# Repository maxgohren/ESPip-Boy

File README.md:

# ESPip-Boy
A smart watch based on the ESP32

# Features
* ESP32 MCU with full Bluetooth Classic
* SD Card storage
* TFT RGB Display
* Flashlight
* Microphone
* Sensors
  * Heart Rate & Blood Oxygen
  * Light Sensor (Auto Display Brightness)
  * Accelerometer (Auto Wakeup, Gestures) 
  * Magnetometer  (Compass)
* Controlled with Push-Button Rotary Encoder

# Planned Applications
* Compass
* Pedometer
* Map/Photo Display
* Clock
* Heart Rate Monitor
* Music Playback
* Bluetooth Manager
* System Monitor (CPU Tasks, SD Storage, RAM Usage etc.)

Powered by a LiPo, charged and programmed over USB

# V1.0 PCB Complete

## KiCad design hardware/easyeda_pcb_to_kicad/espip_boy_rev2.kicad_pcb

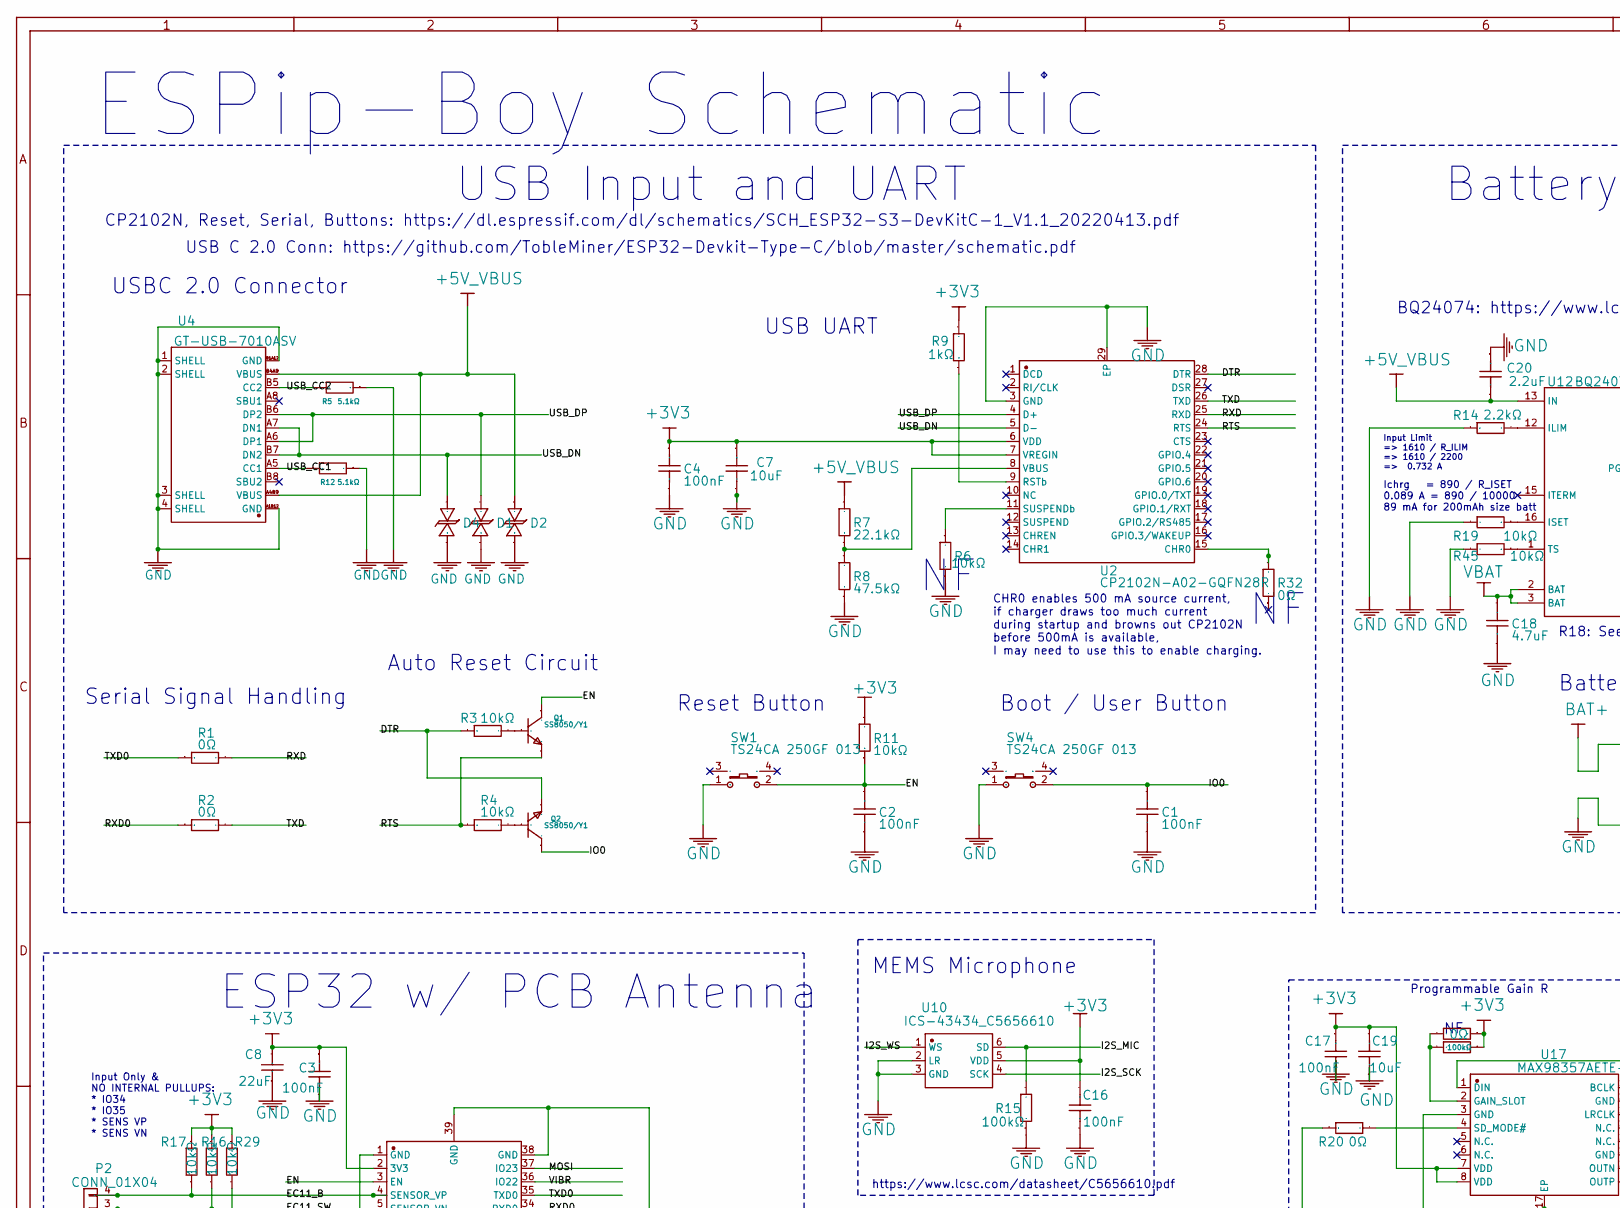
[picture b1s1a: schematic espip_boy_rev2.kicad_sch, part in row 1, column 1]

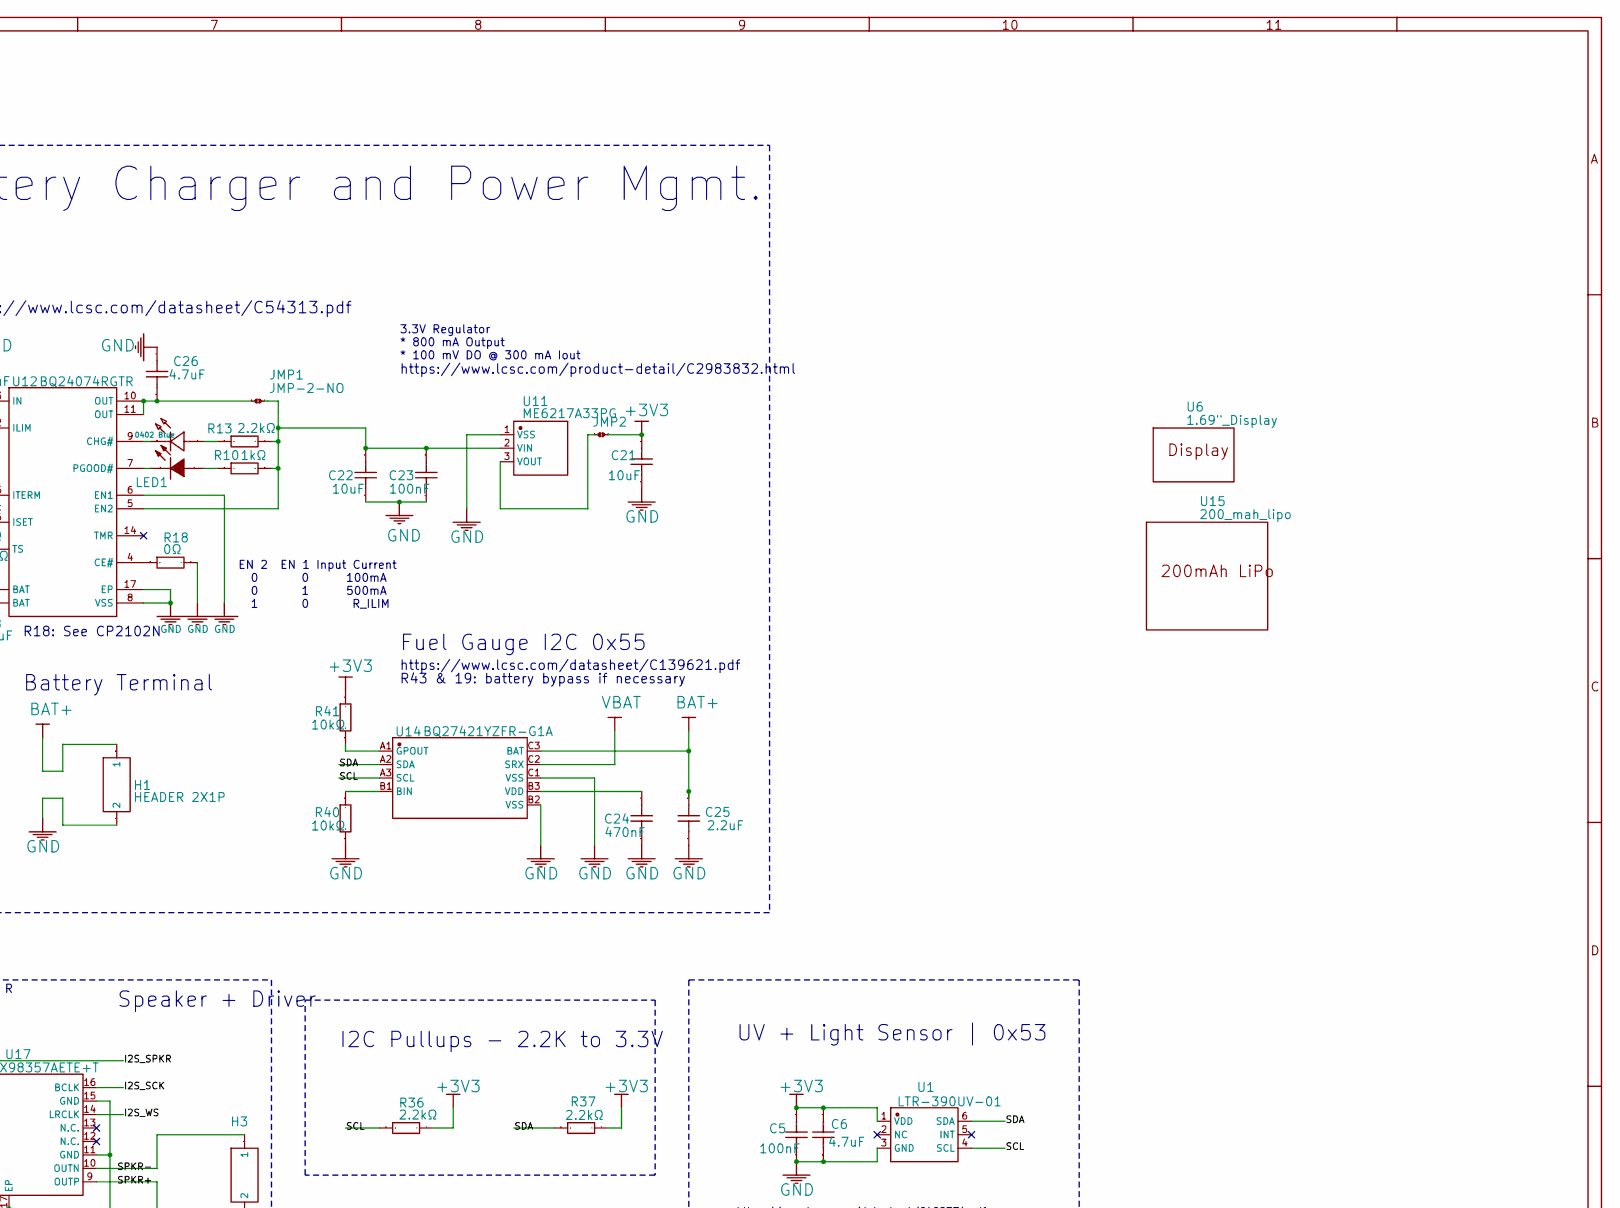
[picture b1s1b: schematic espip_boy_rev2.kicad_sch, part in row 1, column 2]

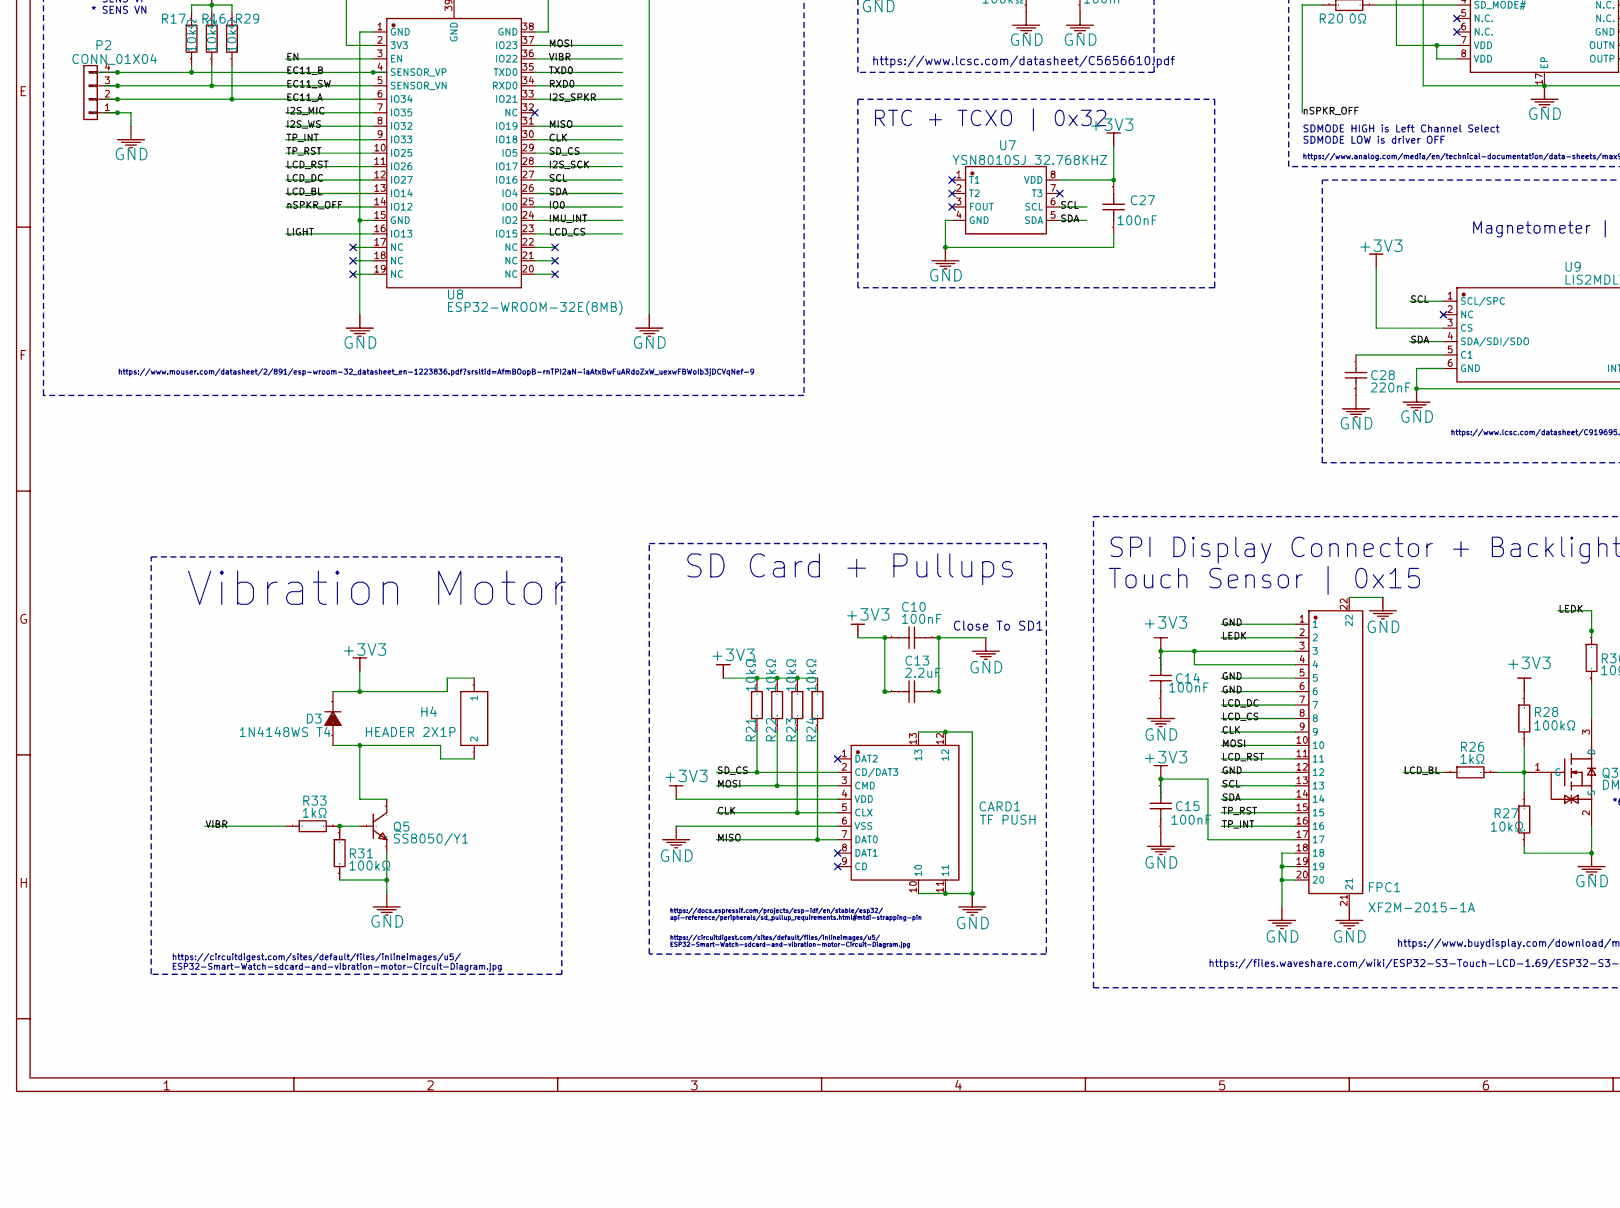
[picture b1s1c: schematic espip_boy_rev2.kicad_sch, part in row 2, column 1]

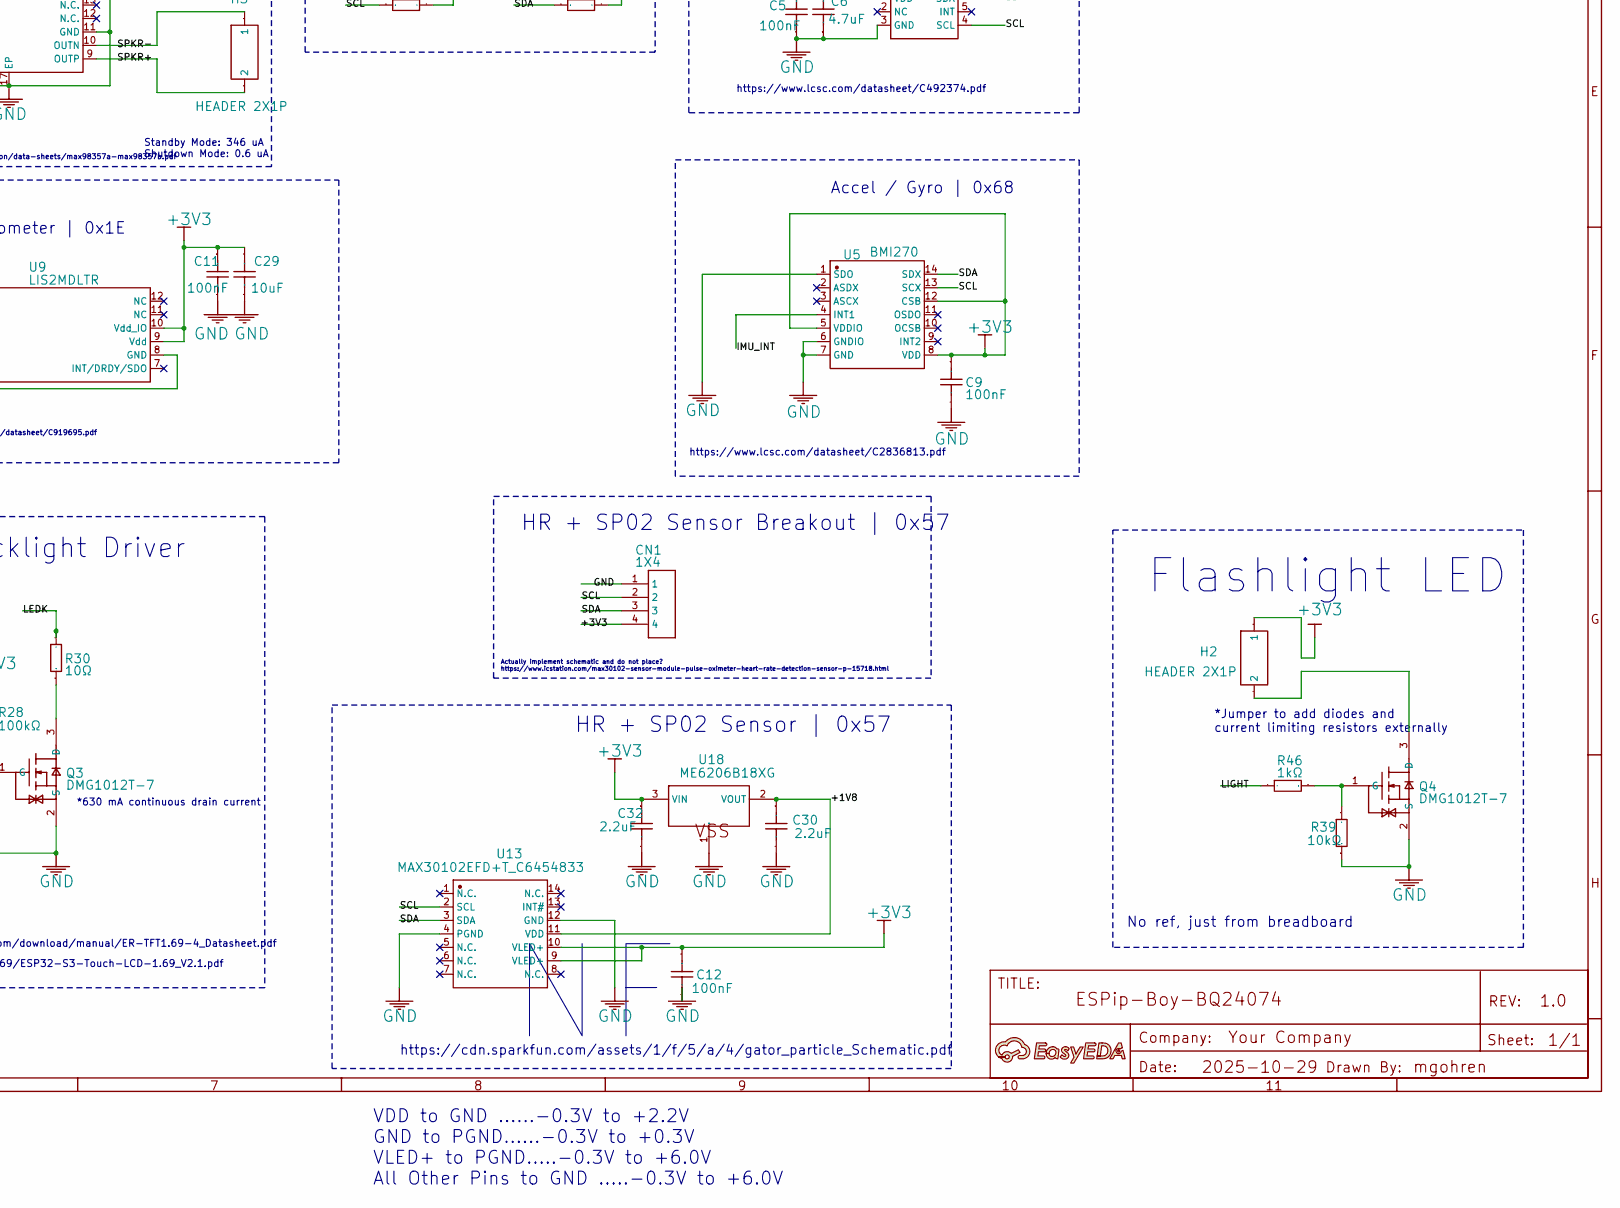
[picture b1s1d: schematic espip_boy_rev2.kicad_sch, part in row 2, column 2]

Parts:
A1: A; SW-SMD_L4.7-W3.5-P3.35-EH; Manufacturer Part ?
C1, C2, C3, C4, C5, C9, C10, C11, C12, C14, C15, C16, C17, C23, C27: 100nF; C_0402_1005Metric; Manufacturer Part CL05B104KO5NNNC
C6, C18, C26: 4.7uF; C_0402_1005Metric; Manufacturer Part CL05A475KP5NRNC
C7, C19, C21, C22, C29: 10uF; C_0402_1005Metric; Manufacturer Part CL05A106MP5NUNC
C8: 22uF; C_0805_2012Metric; Manufacturer Part CL21A226MPQNNNE
C13, C20, C25, C30, C32: 2.2uF; C_0402_1005Metric; Manufacturer Part CL05A225KO5NQNC
C24: 470nF; C_0402_1005Metric; Manufacturer Part CL05A474KA5NNNC
C28: 220nF; C_0402_1005Metric; Manufacturer Part CL05B224KO5NNNC
CARD1: TF PUSH; TF-SMD_TF-PUSH; Manufacturer Part TF PUSH
CN1: 1X4
D1, D2, D4: LESD5D5.0CT1G_C5199850; D_SOD-523; Manufacturer Part LESD5D5.0CT1G
D3: 1N4148WS T4; Manufacturer Part 1N4148WS
FPC1: XF2M-2015-1A; FPC-SMD_20P-P0.50_XF2M-2015-1A; Manufacturer Part XF2M-2015-1A
H1, H2, H3, H4: HEADER 2X1P; Manufacturer Part None
JMP1, JMP2: JMP-2-NO
LED1: TZ-P2-0402YGTIA1-0.45T; LED_0402_1005Metric; Manufacturer Part TZ-P2-0402YGTIA1-0.45T
P2: CONN_01X04
Q1, Q2, Q5: SS8050/Y1; TSOT-23; Manufacturer Part SS8050/Y1
Q3, Q4: DMG1012T-7; SOT-523; Manufacturer Part DMG1012T-7
R1, R2, R18, R20, R32, R38: 0Ω; R_0402_1005Metric; Manufacturer Part 0402WGF0000TCE
R3, R4, R6, R11, R16, R17, R19, R21, R22, R23, R24, R27, R29, R39, R40, R41, R45: 10kΩ; R_0402_1005Metric; Manufacturer Part 0402WGF1002TCE
R5, R12: 5.1kΩ; R_0402_1005Metric; Manufacturer Part 0402WGF5101TCE
R7: 22.1kΩ; R_0402_1005Metric; Manufacturer Part 0402WGF2212TCE
R8: 47.5kΩ; R_0402_1005Metric; Manufacturer Part 0402WGF4752TCE
R9, R10, R26, R33, R46: 1kΩ; R_0402_1005Metric; Manufacturer Part 0402WGF1001TCE
R13, R14, R36, R37: 2.2kΩ; R_0402_1005Metric; Manufacturer Part 0402WGF2201TCE
R15, R28, R31, R35: 100kΩ; R_0402_1005Metric; Manufacturer Part 0402WGF1003TCE
R30: 10Ω; R_0402_1005Metric; Manufacturer Part 0402WGF100JTCE
SW1, SW4: TS24CA 250GF 013; SW-SMD_L4.7-W3.5-P3.35-EH; Manufacturer Part TS24CA 250gf 013
U1: LTR-390UV-01; SENSOR-SMD_LTR-390UV-01; Manufacturer Part LTR-390UV-01
U2: CP2102N-A02-GQFN28R; QFN-28-1EP_5x5mm_P0.5mm_EP3.35x3.35mm_ThermalVias; Manufacturer Part CP2102N-A02-GQFN28R
U3: 0402 Blue; LED_0402_1005Metric; Manufacturer Part XL-1005UBC
U4: GT-USB-7010ASV; USB-C-SMD_G-SWITCH_GT-USB-7010ASV; Manufacturer Part GT-USB-7010ASV
U5: BMI270; LGA-14_L3.0-W2.5-P0.50-BR; Manufacturer Part BMI270
U6: 1.69"_Display
U7: YSN8010SJ 32.768KHZ; SOP-8_L4.9-W3.9-P1.27-LS6.0-BL; Manufacturer Part YSN8010SJ 32.768KHZ
U8: ESP32-WROOM-32E(8MB); ESP32-WROOM-32E; Manufacturer Part ESP32-WROOM-32E-N8
U9: LIS2MDLTR; LGA-12_L2.0-W2.0-P0.50-BL; Manufacturer Part LIS2MDLTR
U10: ICS-43434_C5656610; MIC-SMD_6P-L3.5-W2.7-P0.90-BL; Manufacturer Part ICS-43434
U11: ME6217A33PG; SOT-89-3; Manufacturer Part ME6217A33PG
U12: BQ24074RGTR; TQFN-16_L3.0-W3.0-P0.50-BL-EP1.5; Manufacturer Part BQ24074RGTR
U13: MAX30102EFD+T_C6454833; OESIP-14_L5.6-W3.3-P0.80-TL; Manufacturer Part MAX30102EFD+T
U14: BQ27421YZFR-G1A; DSBGA-9_L1.5-W1.5-R3-C3-P0.50-BL; Manufacturer Part BQ27421YZFR-G1A
U15: 200_mah_lipo
U17: MAX98357AETE+T; TQFN-16_L3.0-W3.0-P0.50-BL-EP1.5; Manufacturer Part MAX98357AETE+T
U18: ME6206B18XG; TSOT-23; Manufacturer Part ME6206B18XG

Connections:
+3V3: C3.1, C4.1, C5.1, C6.2, C7.1, C8.2, C9.1, C10.1, C11.1, C12.1, C13.2, C14.1, C15.1, C16.2, C17.1, C19.2, C21.1, C27.1, C29.2, C32.1, CARD1.4 (VDD), CN1.4, D3.1 (K), FPC1.3, FPC1.4, FPC1.17, H2.1, H4.1, JMP2.2, R9.2, R11.2, R16.1, R17.1, R21.2, R22.2, R23.2, R24.2, R28.1, R29.1, R35.1, R36.2, R37.2, R38.1, R41.2, U1.1 (VDD), U2.6 (VDD), U2.7 (VREGIN), U5.5 (VDDIO), U5.8 (VDD), U5.12 (CSB), U7.8 (VDD), U8.2 (3V3), U9.3 (CS), U9.9 (Vdd), U9.10 (Vdd_IO), U10.5 (VDD), U13.9 (VLED+), U13.10 (VLED+), U17.7 (VDD), U17.8 (VDD), U18.3 (VIN)
+5V_VBUS: C20.2, D2.2, R7.2, U4.A4B9 (VBUS), U4.B4A9 (VBUS), U12.13 (IN)
/+1V8: C30.1, U13.11 (VDD), U18.2 (VOUT)
/CLK: CARD1.5 (CLX), FPC1.9, R23.1, U8.30 (IO18)
/DTR: Q2.2 (E), R3.1, U2.28 (DTR)
/EC11_A: P2.2, R29.2, U8.6 (IO34)
/EC11_B: P2.4, R17.2, U8.4 (SENSOR_VP)
/EC11_SW: P2.3, R16.2, U8.5 (SENSOR_VN)
/EN: C2.1, Q1.3 (C), R11.1, SW1.2, U8.3 (EN)
/I2S_MIC: R15.2, U8.7 (IO35), U10.6 (SD)
/I2S_SCK: U8.28 (IO17), U10.4 (SCK), U17.16 (BCLK)
/I2S_SPKR: U8.33 (IO21), U17.1 (DIN)
/I2S_WS: U8.8 (IO32), U10.1 (WS), U17.14 (LRCLK)
/IMU_INT: U5.4 (INT1), U8.24 (IO2)
/IO0: C1.1, Q2.3 (C), SW4.2, U8.25 (IO0)
/LCD_BL: R26.2, U8.13 (IO14)
/LCD_CS: FPC1.8, U8.23 (IO15)
/LCD_DC: FPC1.7, U8.12 (IO27)
/LCD_RST: FPC1.11, U8.11 (IO26)
/LEDK: FPC1.2, R30.2
/LIGHT: R46.2, U8.16 (IO13)
/MISO: CARD1.7 (DAT0), R24.1, U8.31 (IO19)
/MOSI: CARD1.3 (CMD), FPC1.10, R22.1, U8.37 (IO23)
/RTS: Q1.2 (E), R4.1, U2.24 (RTS)
/RXD: R1.2, U2.25 (RXD)
/RXD0: R2.1, U8.34 (RXD0)
/SCL: CN1.2, FPC1.13, R36.1, U1.4 (SCL), U5.13 (SCX), U7.6 (SCL), U8.27 (IO16), U9.1 (SCL/SPC), U13.2 (SCL), U14.A3 (SCL)
/SDA: CN1.3, FPC1.14, R37.1, U1.6 (SDA), U5.14 (SDX), U7.5 (SDA), U8.26 (IO4), U9.4 (SDA/SDI/SDO), U13.3 (SDA), U14.A2 (SDA)
/SD_CS: CARD1.2 (CD/DAT3), R21.1, U8.29 (IO5)
/SPKR+: H3.2, U17.9 (OUTP)
/SPKR-: H3.1, U17.10 (OUTN)
/TP_INT: FPC1.16, U8.9 (IO33)
/TP_RST: FPC1.15, U8.10 (IO25)
/TXD: R2.2, U2.26 (TXD)
/TXD0: R1.1, U8.35 (TXD0)
/USB_CC1: R12.2, U4.A5 (CC1)
/USB_CC2: R5.2, U4.B5 (CC2)
/USB_DN: D4.2, U2.5 (D-), U4.A7 (DN1), U4.B7 (DN2)
/USB_DP: D1.2, U2.4 (D+), U4.A6 (DP1), U4.B6 (DP2)
/VIBR: R33.2, U8.36 (IO22)
/nSPKR_OFF: R20.1, U8.14 (IO12)
BAT+: C25.1, H1.1, U14.C3 (BAT)
GND: C1.2, C2.2, C3.2, C4.2, C5.2, C6.1, C7.2, C8.1, C9.2, C10.2, C11.2, C12.2, C13.1, C14.2, C15.2, C16.1, C17.2, C18.1, C19.1, C20.1, C21.2, C22.2, C23.2, C24.1, C25.2, C26.2, C27.2, C28.1, C29.1, C30.2, C32.2, CARD1.6 (VSS), CARD1.10, CARD1.11, CARD1.12, CARD1.13, CN1.1, D1.1, D2.1, D4.1, FPC1.1, FPC1.5, FPC1.6, FPC1.12, FPC1.18, FPC1.19, FPC1.20, FPC1.21, FPC1.22, H1.2, P2.1, Q3.2 (S), Q4.2 (S), Q5.2 (E), R5.1, R6.1, R8.1, R12.1, R14.1, R15.1, R18.2, R19.2, R27.1, R31.1, R39.1, R40.1, R45.2, SW1.1, SW4.1, U1.3 (GND), U2.3 (GND), U2.29 (EP), U4.1 (SHELL), U4.2 (SHELL), U4.3 (SHELL), U4.4 (SHELL), U4.A1B12 (GND), U4.B1A12 (GND), U5.1 (SDO), U5.6 (GNDIO), U5.7 (GND), U7.4 (GND), U8.1 (GND), U8.15 (GND), U8.38 (GND), U8.39 (GND), U9.6 (GND), U9.8 (GND), U10.2 (LR), U10.3 (GND), U11.1 (VSS), U12.6 (EN1), U12.8 (VSS), U12.17 (EP), U13.4 (PGND), U13.12 (GND), U14.B2 (VSS), U14.C1 (VSS), U17.3 (GND), U17.11 (GND), U17.15 (GND), U17.17 (EP), U18.1 (VSS)
unnamed: C26.1, JMP1.1, U12.10 (OUT), U12.11 (OUT)
unnamed: D3.2 (A), H4.2, Q5.3 (C)
unnamed: LED1.2, R10.2
unnamed: Q1.1 (B), R3.2
unnamed: Q2.1 (B), R4.2
unnamed: Q3.3 (D), R30.1
unnamed: Q3.1 (G), R26.1, R27.2, R28.2
unnamed: H2.2, Q4.3 (D)
unnamed: Q4.1 (G), R39.2, R46.1
unnamed: Q5.1 (B), R31.2, R33.1
unnamed: R32.2, U2.15 (CHR0)
unnamed: R9.1, U2.9 (RSTb)
unnamed: R6.2, U2.11 (SUSPENDb)
unnamed: R7.1, R8.2, U2.8 (VBUS)
unnamed: R13.1, U3.2 (A)
unnamed: C28.2, U9.5 (C1)
unnamed: C22.1, C23.1, JMP1.2, R10.1, R13.2, U11.2 (VIN), U12.5 (EN2)
unnamed: JMP2.1, U11.3 (VOUT)
unnamed: R18.1, U12.4 (CE#)
unnamed: U3.1 (K), U12.9 (CHG#)
unnamed: R14.2, U12.12 (ILIM)
unnamed: R19.1, U12.16 (ISET)
unnamed: LED1.1, U12.7 (PGOOD#)
unnamed: R45.1, U12.1 (TS)
unnamed: R40.2, U14.B1 (BIN)
unnamed: R41.1, U14.A1 (GPOUT)
unnamed: C24.2, U14.B3 (VDD)
unnamed: R35.2, R38.2, U17.2 (GAIN_SLOT)
unnamed: R20.2, U17.4 (SD_MODE#)
VBAT: C18.2, U12.2 (BAT), U12.3 (BAT), U14.C2 (SRX)

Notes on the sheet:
HR + SP02 Sensor | 0x57
SPI Display Connector + Backlight Driver Touch Sensor | 0x15
Programmable Gain R
SD Card + Pullups
Battery Terminal
RTC + TCXO | 0x32
Accel / Gyro | 0x68
https://www.analog.com/media/en/technical-documentation/data-sheets/max98357a-max98357b.pdf
Input Only & NO INTERNAL PULLUPS: * IO34 * IO35 * SENS VP * SENS VN
MEMS Microphone
I2C Pullups - 2.2K to 3.3V
Magnetometer | 0x1E
USBC 2.0 Connector
https://www.lcsc.com/datasheet/C5656610.pdf
Auto Reset Circuit
Close To SD1
Boot / User Button
https://files.waveshare.com/wiki/ESP32-S3-Touch-LCD-1.69/ESP32-S3-Touch-LCD-1.69_V2.1.pdf
CP2102N, Reset, Serial, Buttons: https://dl.espressif.com/dl/schematics/SCH_ESP32-S3-DevKitC-1_V1.1_20220413.pdf
*Jumper to add diodes and current limiting resistors externally
https://www.lcsc.com/datasheet/C139621.pdf
R43 & 19: battery bypass if necessary
https://www.lcsc.com/datasheet/C492374.pdf
EN 2 EN 1 Input Current 0 0 100mA 0 1 500mA 1 0 R_ILIM
Fuel Gauge I2C 0x55
Actually implement schematic and do not place? https://www.icstation.com/max30102-sensor-module-pulse-oximeter-heart-rate-detection-sensor-p-15718.html
Flashlight LED
https://www.mouser.com/datasheet/2/891/esp-wroom-32_datasheet_en-1223836.pdf?srsltid=AfmBOopB-rnTPI2aN-iaAtxBwFuARdoZxW_uexwFBWoIb3jDCVqNef-9
USB UART
Input Limit => 1610 / R_ILIM => 1610 / 2200 => 0.732 A
ESPip-Boy Schematic
https://www.buydisplay.com/download/manual/ER-TFT1.69-4_Datasheet.pdf
Battery Charger and Power Mgmt.
3.3V Regulator * 800 mA Output * 100 mV DO @ 300 mA Iout
*630 mA continuous drain current
VDD to GND ......-0.3V to +2.2V GND to PGND......-0.3V to +0.3V VLED+ to PGND.....-0.3V to +6.0V All Other Pins to GND .....-0.3V to +6.0V
No ref, just from breadboard
https://cdn.sparkfun.com/assets/1/f/5/a/4/gator_particle_Schematic.pdf
UV + Light Sensor | 0x53
SDMODE HIGH is Left Channel Select SDMODE LOW is driver OFF

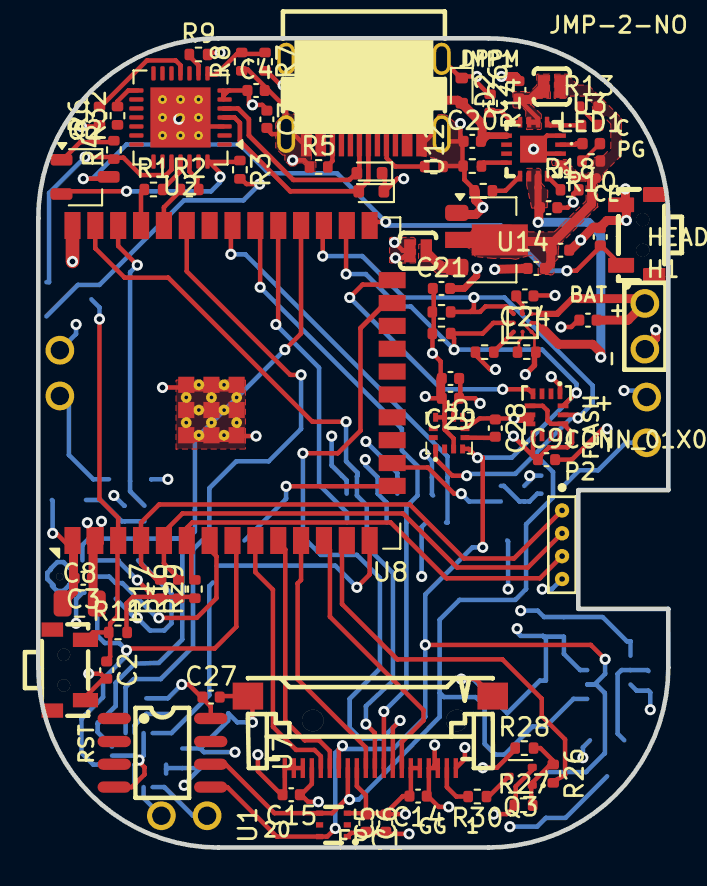
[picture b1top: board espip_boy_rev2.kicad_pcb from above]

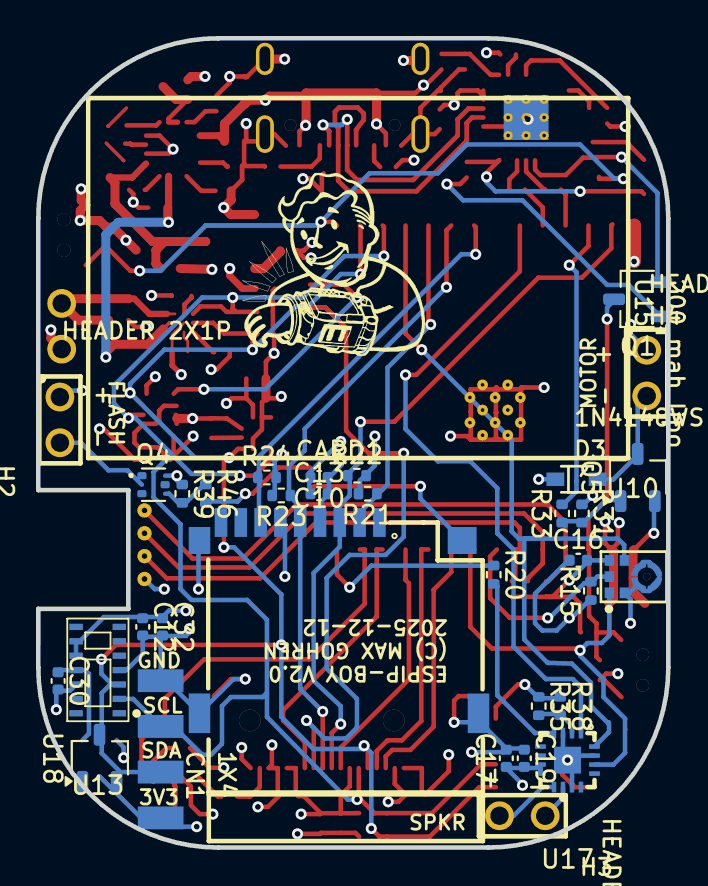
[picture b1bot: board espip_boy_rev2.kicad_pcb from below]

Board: 4 copper layers, 35.0 x 45.0 mm, 111 parts (34 on the bottom side), 73 nets.

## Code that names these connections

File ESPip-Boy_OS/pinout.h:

#pragma once

// ----- Pin Definitions -----
#define LCD_DC     27
#define LCD_RST    26
#define LCD_CS     15
#define LCD_SCK    18
#define LCD_BL     14
#define LCD_MOSI   23

#define IIC_SDA    4
#define IIC_SCL    16

#define TP_RST     25
#define TP_INT     33

#define IMU_INT 2

#define BL_PIN 14

#define LED_PIN 13

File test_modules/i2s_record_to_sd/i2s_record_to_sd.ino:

#include <Arduino.h>
#include <FS.h>
#include <SD.h>
#include <SPI.h>
#include <driver/i2s.h>

// I2S microphone pins
#define I2S_WS 27
#define I2S_SCK 26
#define I2S_SD 35

// SD card SPI pins
#define SD_CS 5
#define SD_MOSI 23
#define SD_MISO 19
#define SD_CLK 18

#define I2S_SAMPLE_RATE 16000
#define I2S_BITS_PER_SAMPLE I2S_BITS_PER_SAMPLE_16BIT
#define I2S_NUM_CHANNELS 1
#define RECORD_TIME_SEC 30  // recording length in seconds
#define WAV_FILENAME "/test.wav"

// I2S config
i2s_config_t i2s_config = {
  .mode = (i2s_mode_t)(I2S_MODE_MASTER | I2S_MODE_RX),
  .sample_rate = I2S_SAMPLE_RATE,
  .bits_per_sample = I2S_BITS_PER_SAMPLE,
  .channel_format = I2S_CHANNEL_FMT_ONLY_LEFT,
  .communication_format = I2S_COMM_FORMAT_I2S,
  .intr_alloc_flags = 0,
  .dma_buf_count = 4,
  .dma_buf_len = 1024,
  .use_apll = false
};

i2s_pin_config_t pin_config = {
  .bck_io_num = I2S_SCK,
  .ws_io_num = I2S_WS,
  .data_out_num = -1, // not used
  .data_in_num = I2S_SD
};

void writeWavHeader(File &file, uint32_t sampleRate, uint32_t bitsPerSample, uint32_t channels, uint32_t dataLength) {
  uint32_t byteRate = sampleRate * channels * bitsPerSample / 8;
  uint16_t blockAlign = channels * bitsPerSample / 8;

  file.seek(0);
  file.write((const uint8_t*)"RIFF", 4);
  uint32_t chunkSize = 36 + dataLength;
  file.write((const uint8_t*)&chunkSize, 4);
  file.write((const uint8_t*)"WAVE", 4);

  // fmt subchunk
  file.write((const uint8_t*)"fmt ", 4);
  uint32_t subChunk1Size = 16;
  file.write((const uint8_t*)&subChunk1Size, 4);
  uint16_t audioFormat = 1; // PCM
  file.write((const uint8_t*)&audioFormat, 2);
  file.write((const uint8_t*)&channels, 2);
  file.write((const uint8_t*)&sampleRate, 4);
  file.write((const uint8_t*)&byteRate, 4);
  file.write((const uint8_t*)&blockAlign, 2);
  file.write((const uint8_t*)&bitsPerSample, 2);

  // data subchunk
  file.write((const uint8_t*)"data", 4);
  file.write((const uint8_t*)&dataLength, 4);
}

void setup() {
  Serial.begin(115200);

  // Init SD card
  SPI.begin(SD_CLK, SD_MISO, SD_MOSI, SD_CS);
  if(!SD.begin(SD_CS)){
    Serial.println("SD Card mount failed!");
    while(1);
  }

  // Create WAV file
  File wavFile = SD.open(WAV_FILENAME, FILE_WRITE);
  if(!wavFile){
    Serial.println("Failed to open file for writing");
    while(1);
  }

  // Placeholder WAV header (we will rewrite later)
  writeWavHeader(wavFile, I2S_SAMPLE_RATE, 16, 1, 0);

  // Init I2S
  i2s_driver_install(I2S_NUM_0, &i2s_config, 0, NULL);
  i2s_set_pin(I2S_NUM_0, &pin_config);

  // Record
  uint32_t sampleCount = I2S_SAMPLE_RATE * RECORD_TIME_SEC;
  int16_t buffer[512];
  uint32_t bytesWritten = 0;

  Serial.println("Recording...");

  while(sampleCount > 0){
    size_t bytesRead;
    uint32_t toRead = min(sampleCount, (uint32_t)(sizeof(buffer)/sizeof(buffer[0])));
    i2s_read(I2S_NUM_0, buffer, toRead * 2, &bytesRead, portMAX_DELAY);
    wavFile.write((uint8_t*)buffer, bytesRead);
    bytesWritten += bytesRead;
    sampleCount -= bytesRead / 2;
  }

  Serial.println("Recording finished");

  // Rewrite WAV header with actual data length
  writeWavHeader(wavFile, I2S_SAMPLE_RATE, 16, 1, bytesWritten);

  wavFile.close();
  i2s_driver_uninstall(I2S_NUM_0);
}

void loop() {
  // Nothing here
}

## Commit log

2025-07-11 Added devlogs folder
2025-07-11 Added mp3 bt test
2025-07-11 Interfaced with LSM303
2025-07-13 GPS Module testing complete!
2025-07-15 Attempted TFT Display
2025-07-15 TFT .ino
2025-07-16 Interfaced succesfully with the TFT Display!
2025-07-16 Started the PCB schematic!
2025-08-02 Starting August off with some more PCB design: adding connections to my USB Serial chip!
2025-08-16 EC11 test finished
2025-08-16 Added EC11 reading and resources
2025-08-17 EC11 schematic done, looking into batteries and associated ICs now
2025-08-18 SD Card TEST Success!
2025-08-18 August devlog update
2025-08-19 A system is emerging
2025-08-21 Menu with clock, cube and buzzer app! Finalizing design components as prototyping comes to an end
2025-08-21 Added docs from work computer
2025-08-22 gitignore obsidian
2025-08-22 Devlog
2025-08-26 Component selection
2025-08-27 Headphones test with bluetooth. Researching antenna performance and PMICs
2025-08-27 antenna and usbc reading/resources devlog
2025-08-28 Microphone selection
2025-08-28 More component research
2025-08-29 TRAIN KEEPS ROLLING! USBC CONNECTOR DONE ON SCHEMATIC!
2025-09-03 Schematic time
2025-09-09 Waiting for power hardware, working on LVGL graphics now
2025-09-10 Got LVGL demo kinda working
2025-09-11 LVGL why are you so difficult!
2025-09-12 New breadboard and display
2025-09-13 fixed broken image link
2025-09-13 LVGL test completed on new display! It's awesome!
2025-09-13 Added demo video to devlog
2025-09-13 Shorter video to be able to size within GitHub 10MB limit
2025-09-13 Update September2025-SchematicTime.md
    Added video
2025-09-18 Added MAX98357 amp to breadboard and got a noisy speaker working
2025-09-25 Microphone and speaker working
2025-09-26 Fuel gauge test and nearing completion of prototype!
2025-10-01 Microphone recording and playback!
2025-10-02 A new month and a new mindset!
2025-10-03 Learning to decode a WAV file
2025-10-04 Cleaned up schematic to update with recent prototype changes
2025-10-08 Regulator and fuel gauge finished on the schematic
2025-10-09 Schematic is roughly complete.
2025-10-10 Added lvgl test
2025-10-13 Simulated simple NPN flashlight LED driver
2025-10-17 Flashlight driver added to schematic
2025-10-21 LED Flashlight PWM driver - 20mA is so bright
    >
2025-10-22 Got the LED driver working perfectly
2025-10-23 Some final hardware validations before moving onto the first round of PCB design
2025-10-24 Flashlight driver devlog
2025-10-29 Finshed V1.0 of the PCB. Time to check it over, order and cross my fingers!
2025-10-30 V1.0 of PCB complete!
2025-10-30 Fix README img link
2025-10-30 Remove GPS feature
2025-11-01 Reviewed design, found display conn. is backwards :(
2025-11-06 USB diff. pair and added MAX30102 footprint. Cleaning up BOM. Need replacement I2S mic
2025-11-26 It's alive
2025-11-30 Renamed firmware source. Added case files
2025-11-30 ESPip-Boy_OS updated to just watchface
2025-12-01 Added orientation based display toggle
2025-12-02 Added digital clock and wifi NTP clock sync.
2025-12-03 Almost to a useable state now
2025-12-04 Added loading screen and date. Changed time format to 12 hours with AM/PM. I love you strftime
2025-12-09 Clean up project, clean up kicad sch, learned split in FreeCAD for clamshell case design improvement
2025-12-11 Placed some more components for V2.0
2025-12-13 V2.0 finished. All hardware verified, only motor and microphone not working as expected
2025-12-18 Penultimate? review of Rev2 pcb. Interfaced with more I2C devices to confirm working state
2025-12-20 Ordered Rev2 PCB
2025-12-27 Imported ESPip-Boy Rev2 pcb into KiCAD to get .STEP export
2025-12-28 Completed assembly of Rev 2 pcb, battery, display and digital crown
2025-12-30 Rev2 assembled and working
2025-12-31 Trouble in FreeCAD time
2025-12-31 Goofy case design sent to print shop
2026-01-02 Sent 20mm lug split case with M1.2 screw holes to printer
2026-01-06 Fixed shell lip misalignment
2026-01-12 Clock/wifi/rtc time sync updates, sleep and wakeup updates, flashlight added but not fully implemented
2026-01-14 Add battery configuration to 200mAh, add todos for even deeper sleep
2026-01-14 Case complete, spicing up the UI with LVGL and EEZ Studio
2026-01-15 Added termiwatch inspired UI. Huge refactor of code to modules.
2026-01-15 Fixed RTC and wake logic to update time from RTC after 0th boot which updates from WiFi
2026-01-15 Fix wifi time update not updating RTC
2026-01-16 Cleaned up IMU logic, decoupled screen sleep from esp32 sleep, started implementing pwm for led and bl but not finished yet
2026-01-16 Added display backlight fading in and out! Now to fix LED
2026-01-16 Got flashlight fade in working with button press
2026-01-19 Added low power mode for IMU. Moved source into .cpp files to solve circular include problem of header only implementations
2026-02-05 Fixed display with correct offset. Added double tap to turn on flashlight
2026-02-11 Add FreeRTOS tasks for display fade and display update so that time is always highest priority update
2026-02-11 Added eez-ui for LVGL ui creation and test folders to .gitignore
2026-02-13 Updated .gitignore
2026-02-13 Updating secrets again
2026-02-13 Brought project into VSCode
2026-02-13 Refactored lots of header only implementations into classes with global extern instance.
    Also added rough weather update with API and task to update. Currently updates every 15 hours and returns closest forecast data. Need to clean up and add WiFi mutex, possibly batch together with star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
2026-02-18 Updated knob and added stls for printing
2026-03-02 Added task monitor task. Added debug print calls.
2026-03-02 Replaced all serial commands with debug commands
2026-03-03 Lower imu polling rate to save battery
2026-03-10 Changed to use configTzTime to handle DST automatically
2026-03-10 Remove setenv() and tz() calls as they are done inside configTzTime() now
2026-03-14 Added WiFi manager to share wifi code between clock and weather apps.
2026-03-16 Add test sketches and eez-ui without generated code (updated .gitignore to ignore eez-ui gen. code
2026-03-29 Add new case V3 with covered antenna and compliant IO0 button. Early return from weather service until wifi manager is implemented
2026-03-29 Remove wifi_mgr, will add correct one after
